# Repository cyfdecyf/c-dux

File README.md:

# C. Dux Keyboard

C. Dux front               |  C. Dux back
:-------------------------:|:-------------------------:
  |  

**C. Dux** is a 38-key split wireless keyboard inspired by
[**rae-dux**](https://github.com/andrewjrae/rae-dux) and
[**Architeuthis Dux**](https://github.com/tapioki/cephalopoda/tree/main/Architeuthis%20dux) (A. Dux).

## Features

- **Split Design**: 38-key, mainly 3x5 column-staggered layout, **3 thumb keys and 1 extra pinky key**
- **Choc v1 switch, optional hot-swap sockets**
- **Uses ZMK firmware**
- **Rotary encoder** placed near thumb, easy to reach
- **Diodless Reversible PCB**: Single PCB design that can be used for both left and right halves

Note: I did not consider designing a case when I designed the PCB, as I use the
keyboard with naked PCB. A 3D printed vertical stand came later, see
[3D printed case](#3d-printed-case) below.
So it's better to use leadless PCB and solder. I find SAC305 solder (with 380-degree solder iron)
is a little harder to use compared to Tin-Lead 63/37 solder (with 280-degree solder iron),
but not too much.

## Differences with rae-dux:

- **One extra key for little finger**
  - C. Dux [v1 uses 36-key](./pcb/v1.0/c-dux-front.png), but as a long time Vim user who uses Capslock as Esc, I
    missed the efficiency of pressing Esc with pinky. So I added the extra pinky key.
- **Supports EC11/EC12 rotary encoder**
  - I use the left encoder for left, right arrow keys, the right one for up and
    down. With layer switching, they are also used for page up/down, alt f/b (in
    shell), ctrl-tab/ctrl-shift-tab.
- **Using [ProMicro NRF52840](https://www.nologo.tech/product/otherboard/NRF52840.html) as controller**
  - I choose diodeless design to make things simple. With vanilla ProMicro's 18 GPIO pins, I
    can only build a 36-key keyboard.
  - Both [nice!nano](https://nicekeyboards.com/nice-nano/) and ProMicro NRF52840 provides 3 extra pins,
    which allows adding rotary encoder and one extra key. But the physical position for the 3 extra
    pins on those two controllers are not the same, so they are not fully compatible.
- **With mounting holes to for [Tenting Puck](https://splitkb.com/products/tenting-puck)**
  - Using only 3 holes, took the design from A. Dux
- **M4 holes for other mounting options**

The keyboard layout and PCB is generated using [Ergogen](https://github.com/ergogen/ergogen) v4.
Traces are added manually in KiCAD 8.
I learned how to use Ergogen form [FlatFootFox](https://flatfootfox.com/)'s
[Let's Design A Keyboard With Ergogen v4](https://flatfootfox.com/ergogen-introduction/) series articles,
highly recommended!

## Configurations

Refer to my [zmk-config](https://github.com/cyfdecyf/zmk-config) repo. I do
local build, github workflow is not tested.

Some combos are inspired by [Glove80 TailorKey](https://sites.google.com/view/keyboards/glove80_tailorkey).
(I own one [Moergo's Glove80](https://www.moergo.com/). It's a great keyboard. I
started using home-row mod with Glove80.)

## PCB files

Here's [v2.0 PCB gerbers file](./pcb/v2.0/c-dux-gerbers.zip). You can download
the file and place order from JLC.
I made a few fixes for problems found after I got the PCB from JLC, so it's not
exactly the same file I've used but should work without problems.

## Tips for using Ergogen with KiCAD

For non-key footprints (power/reset switches, etc.), my workflow is:

1. Generate the footprint in PCB with Ergogen at arbitrary position
2. Place the footprint in KiCAD with mouse
3. Use KiCAD ruler to find relative position to some key
4. Update the footprint position in Ergogen yaml file

## My own build

As I suffer from RSI, I choose the 20g pink Choc v1 switches (which is the lightest switches I know).
For keycaps, I find the 3D printed saddle variant of
[KLP-Lame-Keycaps](https://github.com/braindefender/KLP-Lame-Keycaps) quite pleasant to use. The keycap
curve makes it easy to press the up & down rows, and helps a lot to position fingers on the home row.

PCBs are ordered from JLC. [Power](https://item.szlcsc.com/2774931.html) and
[reset](https://item.szlcsc.com/299976.html) switch are from LCSC.

### C. Dux v2

I got the idea of mouting keyboard on desk and let hands go twards the ground from
[Ben Vallack](https://www.youtube.com/@BenVallack)'s video
[The Perfect TENTING SOLUTION For Split Keyboards](https://www.youtube.com/watch?v=mT3TToFqqEU).
Check out Ben Vallack's channel if you are interested in ergonomic keyboards.

This is the most comfortable way for me to use a keyboard. **This position helps
a lot to relieve my RSI and I can work all day long without much pain in my forearm**.

### 3D printed case

The keyboard stands vertically on the desk with a 3D printed case, designed with
[build123d](https://github.com/gumyr/build123d). It is a two-piece design: a
shared base (symmetric, printed once) plus an upright that sets the recline
angle. The two parts join with tongue-and-groove keys and 2×M4 screws from the
bottom, so trying a different recline angle only requires reprinting the
upright.

- Usage, parameters and printing guide:
  [case/build123d/README.md](./case/build123d/README.md)
- Code-level design doc: [docs/stand-design.md](./docs/stand-design.md)

### C. Dux v1

This is my first attempt to build a keyboard. The rotary encoder is difficult to reach
which is the biggest mistake I made.

The keycap used in this version is Chosfox's
[CFX](https://chosfox.com/products/chocfox-cfx-choc-keycaps) keycap.
(Search for "哈狐 Chosfox" on Taobao if you live in China.)
This keycap is not as smootch as Moergo's [MCC keycap](https://www.moergo.com/collections/mcc-keycaps),
but it's still quite good and is much cheaper. But as I like the curved keywell of Glove80,
I switched to KLP Lame keycaps later.

## Future plans

I'm quite comfortable with C. Dux v2 and I'm not planning to build an improved version soon.
But I do plan to build a third keyboard for backup.

Here are a few things that I'd like to change:

- Decrease thumb key spacing
  - v2 decrease thumb key spacing compared to v1, but it's still wider
    compared to Glove80's upper thumber cluster
- Change hotswap socket outer hole diameter to 1.72mm
  - v1 uses 1.7mm which is too tight, v2 uses 1.74mm which is a bit loose
- Move rotary encoder a little up to make it easier to reach for index finger
- Remove teardrop for all GND pads to make solding easier
  - Even thermal reliefs teardrop still makes it harder to solder

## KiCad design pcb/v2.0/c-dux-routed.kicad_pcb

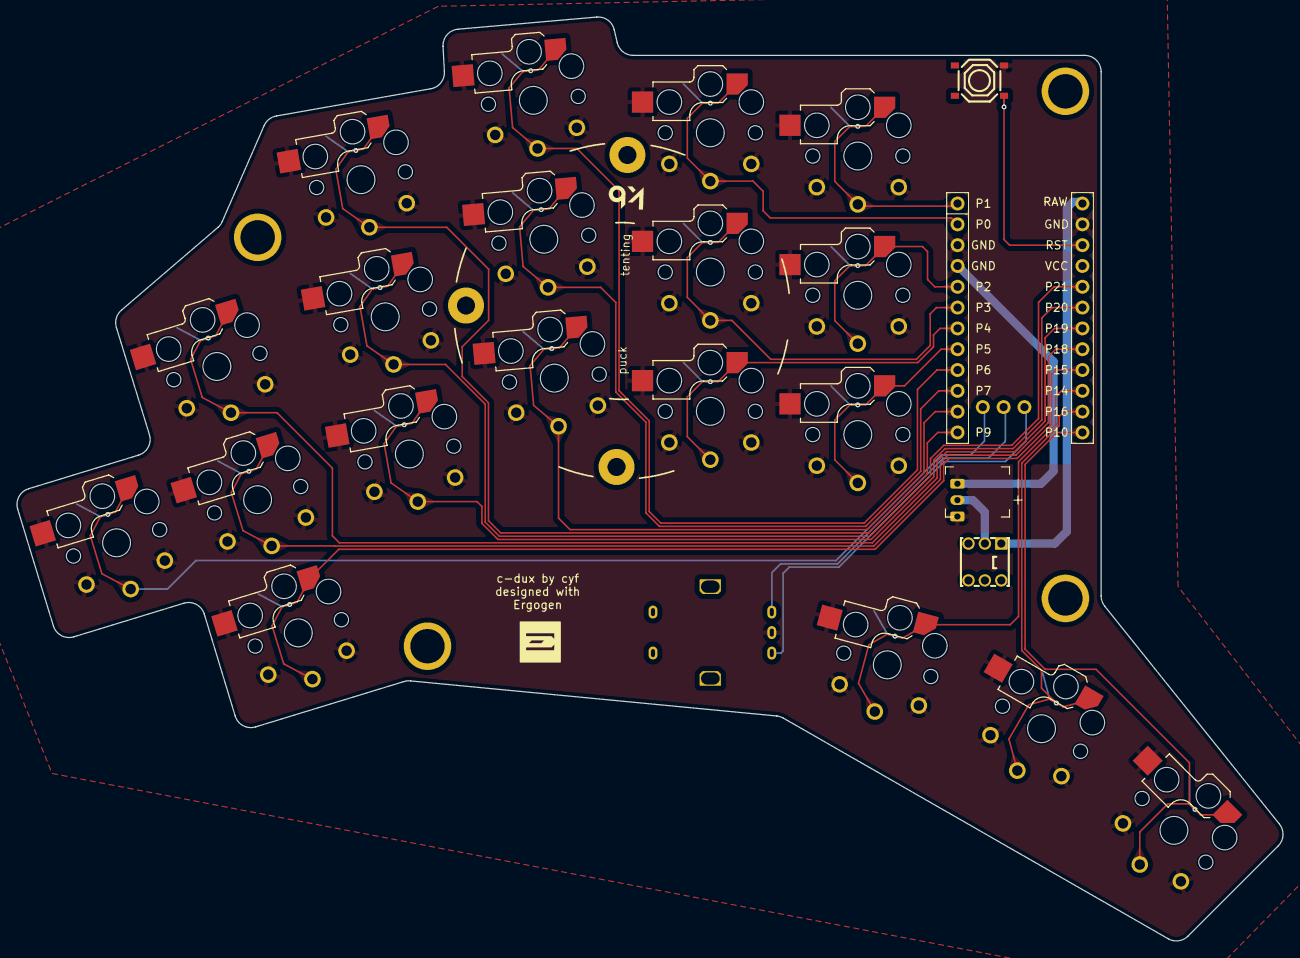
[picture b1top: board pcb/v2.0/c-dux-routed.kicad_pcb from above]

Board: 2 copper layers, 154.5 x 112.8 mm, 30 parts (0 on the bottom side), 25 nets.

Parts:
H1, H2, H3, H4: mounting_hole_plated
JST1: battery_connector_jst_ph_2
LOGO1: utility_ergogen_logo
MCU1: mcu_supermini_nrf52840
RE1: rotary_encoder_ec11_ec12
S1, S2, S3, S4, S5, S6, S7, S8, S9, S10, S11, S12, S13, S14, S15, S16, S17, S18, S19: switch_choc_v1_v2
SW1: SW_Push_Lock; SW-TH_5.8ZSPT
SW2: SW-SMD_4P; SW-SMD_4P-L5.1-W5.1-P3.70-LS6.5-TL_H1.5
TP1: Tenting Puck, no hole; TentingPuck_NoHole

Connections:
BRAW: JST1.2, SW1.2
GND: JST1.1, JST1.3, MCU1.2, MCU1.21, MCU1.22, RE1.B, S1.1, S1.2, S2.1, S2.2, S3.1, S3.2, S4.1, S4.2, S5.1, S5.2, S6.1, S6.2, S7.1, S7.2, S8.1, S8.2, S9.1, S9.2, S10.1, S10.2, S11.1, S11.2, S12.1, S12.2, S13.1, S13.2, S14.1, S14.2, S15.1, S15.2, S16.1, S16.2, S17.1, S17.2, S18.1, S18.2, S19.1, S19.2, SW2.3
P0: MCU1.23, S13.1, S13.2
P1: MCU1.24, S16.1, S16.2
P2: MCU1.20, S15.1, S15.2
P3: MCU1.19, S12.1, S12.2
P4: MCU1.18, S11.1, S11.2
P5: MCU1.17, S14.1, S14.2
P6: MCU1.16, S10.1, S10.2
P7: MCU1.15, S9.1, S9.2
P8: MCU1.14, S8.1, S8.2
P9: MCU1.13, S7.1, S7.2
P10: MCU1.12, S19.1, S19.2
P14: MCU1.10, S17.1, S17.2
P15: MCU1.9, S2.1, S2.2
P16: MCU1.11, S18.1, S18.2
P18: MCU1.8, S3.1, S3.2
P19: MCU1.7, S4.1, S4.2
P20: MCU1.6, S5.1, S5.2
P21: MCU1.5, S6.1, S6.2
P101: MCU1.25, S1.1, S1.2
P102: MCU1.26, RE1.A
P107: MCU1.27, RE1.C
RAW: MCU1.1, SW1.1
RST: MCU1.3, SW2.1

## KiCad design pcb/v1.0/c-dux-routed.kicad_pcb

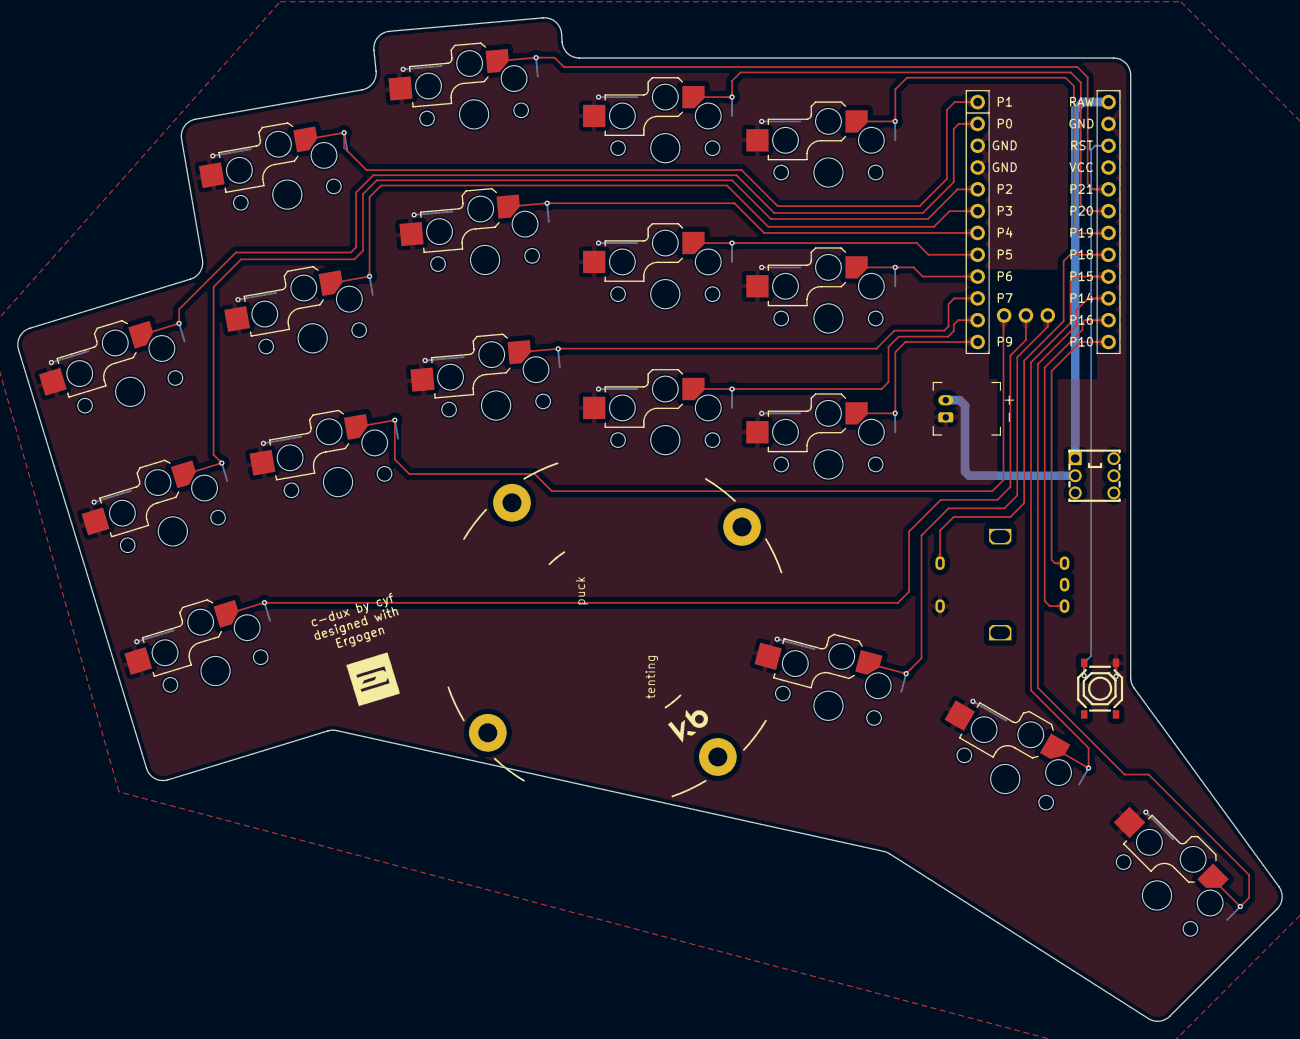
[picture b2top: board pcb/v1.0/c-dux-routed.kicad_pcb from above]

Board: 2 copper layers, 147.3 x 116.9 mm, 25 parts (0 on the bottom side), 25 nets.

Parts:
JST1: battery_connector_jst_ph_2
LOGO1: utility_ergogen_logo
MCU1: mcu_supermini_nrf52840
RE1: rotary_encoder_ec11_ec12
S1, S2, S3, S4, S5, S6, S7, S8, S9, S10, S11, S12, S13, S14, S15, S16, S17, S18: switch_choc_v1_v2
SW1: SW_Push_Lock; SW-TH_5.8ZSPT
SW2: SW-SMD_4P; SW-SMD_4P-L5.1-W5.1-P3.70-LS6.5-TL_H1.5
TP1: Tenting Puck, no hole; TentingPuck_NoHole

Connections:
BRAW: JST1.2, SW1.2
GND: JST1.1, MCU1.2, MCU1.21, MCU1.22, RE1.B, RE1.S1, S1.1, S1.2, S2.1, S2.2, S3.1, S3.2, S4.1, S4.2, S5.1, S5.2, S6.1, S6.2, S7.1, S7.2, S8.1, S8.2, S9.1, S9.2, S10.1, S10.2, S11.1, S11.2, S12.1, S12.2, S13.1, S13.2, S14.1, S14.2, S15.1, S15.2, S16.1, S16.2, S17.1, S17.2, S18.1, S18.2, SW2.1
P0: MCU1.23, S3.1, S3.2
P1: MCU1.24, S6.1, S6.2
P2: MCU1.20, S2.1, S2.2
P3: MCU1.19, S5.1, S5.2
P4: MCU1.18, S8.1, S8.2
P5: MCU1.17, S11.1, S11.2
P6: MCU1.16, S14.1, S14.2
P7: MCU1.15, S7.1, S7.2
P8: MCU1.14, S10.1, S10.2
P9: MCU1.13, S13.1, S13.2
P10: MCU1.12, RE1.A
P14: MCU1.10, S18.1, S18.2
P15: MCU1.9, S17.1, S17.2
P16: MCU1.11, RE1.C
P18: MCU1.8, RE1.S2
P19: MCU1.7, S15.1, S15.2
P20: MCU1.6, S12.1, S12.2
P21: MCU1.5, S9.1, S9.2
P101: MCU1.25, S4.1, S4.2
P102: MCU1.26, S1.1, S1.2
P107: MCU1.27, S16.1, S16.2
RAW: MCU1.1, SW1.1
RST: MCU1.3, SW2.3

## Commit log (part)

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2025-01-31 ergogen: points and outlines.
    Mostly copying from rae-dux and update for ergogen v4.
2025-01-31 submodule: add ceoloide/ergogen-footprints.
2025-01-31 outline: add jst_bat, reset & power button, rotary encoder.
2025-02-01 Remove unnecessary footprint def in points section.
2025-02-07 footprint: add self lock switch from LCSC C2681588.
2025-02-07 pcb: add reset button.
2025-02-07 pcb: add power switch.
2025-02-07 Make inter top cut edge same height with index top.
    This allows moving power & reset button up thus gives more space for rotary encoder.
2025-02-07 footprint: add momentary switch from LCSC C318884.
2025-02-07 pcb: initial add.
    Add hotswap socket, MCU, JST PH 2.0 connector, rotary encoder.
2025-02-07 Use global key.spread.
2025-02-07 Tweak outline.
2025-02-07 footprint: add tenting pack.
2025-02-07 pcb: add tenting puck.
2025-02-07 pcb: add 3d model for rotary encoder.
2025-02-07 pcb: add ergogen logo and c-dux text.
2025-02-09 pcb: use 1.7mm diameter for choc v1 socket outer stabilizer.
2025-02-10 chore(pcb): move rotary section below power button.
2025-02-10 pcb: move tenting puck a little down.
2025-02-10 pcb: mcu disable reverse mount.
2025-02-10 pcb: change net connection.
2025-02-11 Add Ergogen generated KiCAD files.
2025-02-11 kicad: initial routing.
2025-02-11 kicad: finish routing.
    With some manual placement change after routing almost done.
2025-02-11 kicad: update ergogen generated pcb.
2025-02-11 pcb: update layout to match routed board.
2025-02-12 kicad: fill copper zone for both sides, add tear drops.
2025-02-12 kicad: manually remove unnecessary GND line on F.cu layer.
    After copper filling for F.cu, GND lines for choc hotswap socket become
    unnecessary and they have a very small gap with copper filling
    connection to PTH. Thus manually remove them to avoid potential
    problems.
    The problem could be fixed by changing ceoloide/switch_choc_v1_v2.js to
    add some offset for the via hole.
2025-03-04 kicad: manually fix problems found after PCB production.
    1. EC11 through hole should have copper on both layer.
    2. JST connector also have silkscreen on back side.
2025-03-05 submodule: use my own fork of ergogen-footprints with improvements.
2025-03-05 ergogen: include silkscreen on both sides for battery connector.
2025-03-05 Add all PCB related output to pcb/v1.0 folder.
2025-03-16 pcb: increase choc v1 outer stabilizers diameter to 1.74mm.
2025-03-16 pcb: choc v1 enable solder.
    So that hotswap socket is optional.
2025-03-16 pcb: reduce index & inner column spread.
2025-03-16 chore: retab footprint js files.
2025-03-29 pcb: jst ph 2 connector use 3 through holes.
2025-03-29 outline: keep only keys and mcu.
    For other components, let's just place them in KiCAD
    and sync back position in pcb section.
2025-03-29 pcb: choc switch does not include trace for GND pads.
2025-03-29 submodule: update ergogen-footprints for improvements.
2025-03-29 pcb: switch change hotswap pad side option.
2025-03-29 pcb: tenting puck use only three holes, change position.
2025-03-29 key: add one pinker outer column key.
2025-03-29 footprint(tenking_puck): add option to use only 3 holes.
2025-03-29 key: make thumb key more close together and more out.
2025-03-29 keys: reduce column spread.
2025-03-29 pcb: move rotary encoder to beside thumb home key.
2025-03-29 outline: refine to leaf less space around edge.
2025-03-29 pcb: add four M4 mounting holes.
2025-03-29 pcb: rotary encoder only use A, B line.
2025-03-29 pcb: move mcu closer to key, lower for 30mm battery.
2025-03-29 pcb: move battery, reset, power button location.
2025-03-30 pcb: move power button to near edge.
2025-03-30 pcb: move tenting puck to center.
    Learn from Architeuthis dux's placement of tenting puck.
2025-03-31 pcb: move mcu, etc. left, make PCB more compact.
2025-03-31 pcb: give mouting hole 8mm diameter for hex nut.
    Move mcu down to give more room for 701230 LiPo battary (actual length is 32mm).
2025-04-01 pcb: change net to ease routing.
2025-04-02 pcb: change power button rotation for ease of routing.
2025-04-02 pcb: fix tenting puck overlapping with hotswap pd.
    Discovered running DRC check for routing.
2025-04-02 pcb: move mcu 0.2mm left.
    So that copper fill can cover mcu edge and connect to GND pin.
2025-04-02 pcb: move rotary encoder 1mm up.
2025-04-02 pcb: move text to not overlap with trace.
2025-04-07 v2.0: add generated and routed KiCAD PCB files.
2025-04-07 chore: add .gitignore.
2025-04-12 chore: comment about choc stabilizer diameter size.
2025-05-10 Add PCB 3D preview image for v2.0.
2025-06-10 chore: add VSCode tasks for ergogen build.
2025-06-11 Add keyboard photos.
2025-06-11 Add README.
2025-06-11 chore: update .gitignore.
2025-06-11 Add license.
2025-09-13 Add photo with m4 threaded bolts.
